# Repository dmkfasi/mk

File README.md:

# mk
# Redraw of arcade Mortal Kombat schematics

I actually messed up this a little bit.
The initial idea was to re-create original schematics from official arcade game manual. I started with freeware verions of
EAGLE, but then moved to KiCAD as an opensource alternative tool with no restrictions to the board size. I have completed
Sound Board only so far but never finished board layout due to high load of discrete components.

Other folders contains:
Arcade Cabinet - few FreeCAD drafts about the cabinet itself,
and
MultiKickHarness - a condenser board to hook up all the auxiliar Low Punch, Low Kick and Run buttons if you happen to have
multiple boards installed into a single cabinet.

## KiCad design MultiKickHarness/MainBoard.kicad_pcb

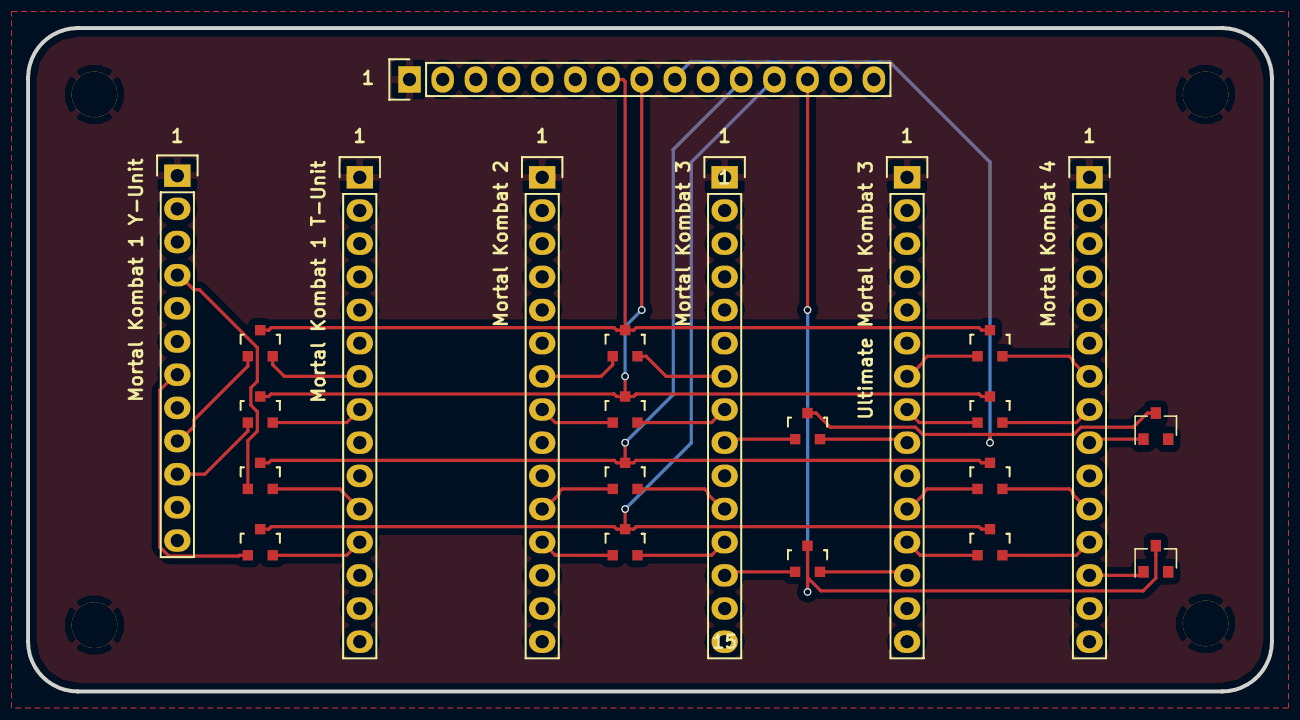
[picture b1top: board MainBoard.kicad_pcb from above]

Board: 2 copper layers, 95.3 x 50.8 mm, 27 parts (0 on the bottom side), 37 nets.

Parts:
D1, D2, D3: P2LP; SOT-23
D4, D5, D14: P2LK; SOT-23
D6, D11, D13: P1LK; SOT-23
D7, D8, D9: P1LP; SOT-23
D10, D15: P1RUN; SOT-23
D12, D16: P2RUN; SOT-23
J1: Mortal Kombat 1 Y-Unit; Pin_Header_Straight_1x12
J2: Mortal Kombat 1 T-Unit; Pin_Header_Straight_1x15
J3: Mortal Kombat 2; Pin_Header_Straight_1x15
J4: Mortal Kombat 3; Pin_Header_Straight_1x15
J5: Ultimate Mortal Kombat 3; Pin_Header_Straight_1x15
J6: Mortal Kombat 4; Pin_Header_Straight_1x15
P0, P0#2, P0#3, P0#4: MOUNTING HOLE; MountingHole_3-5mm
P1: TO CONTROL PANEL; Pin_Header_Straight_1x15

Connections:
/GND: J1.1, J2.1, J3.1, J4.1, J5.1, J6.1, P0.1, P0#2.1, P0#3.1, P0#4.1, P1.1
/P1-LK: D6.3, D11.3, D13.3, P1.8
/P1-LP: D7.3, D8.3, D9.3, P1.7
/P1-RUN: D10.3, D15.3, P1.9
/P2-LK: D4.3, D5.3, D14.3, P1.12
/P2-LP: D1.3, D2.3, D3.3, P1.11
/P2-RUN: D12.3, D16.3, P1.13
unnamed: D1.1, J1.4
unnamed: D1.2, J2.11
unnamed: D2.1, J3.11
unnamed: D2.2, J4.11
unnamed: D3.1, J5.11
unnamed: D3.2, J6.11
unnamed: D4.1, J1.7
unnamed: D4.2, J2.12
unnamed: D5.1, J3.12
unnamed: D5.2, J4.12
unnamed: D6.1, J1.10
unnamed: D6.2, J2.8
unnamed: D7.1, J1.9
unnamed: D7.2, J2.7
unnamed: D8.1, J3.7
unnamed: D8.2, J4.7
unnamed: D9.1, J5.7
unnamed: D9.2, J6.7
unnamed: D10.1, J4.9
unnamed: D10.2, J5.9
unnamed: D11.1, J3.8
unnamed: D11.2, J4.8
unnamed: D12.1, J4.13
unnamed: D12.2, J5.13
unnamed: D13.1, J5.8
unnamed: D13.2, J6.8
unnamed: D14.1, J5.12
unnamed: D14.2, J6.12
unnamed: D15.1, J6.9
unnamed: D16.1, J6.13

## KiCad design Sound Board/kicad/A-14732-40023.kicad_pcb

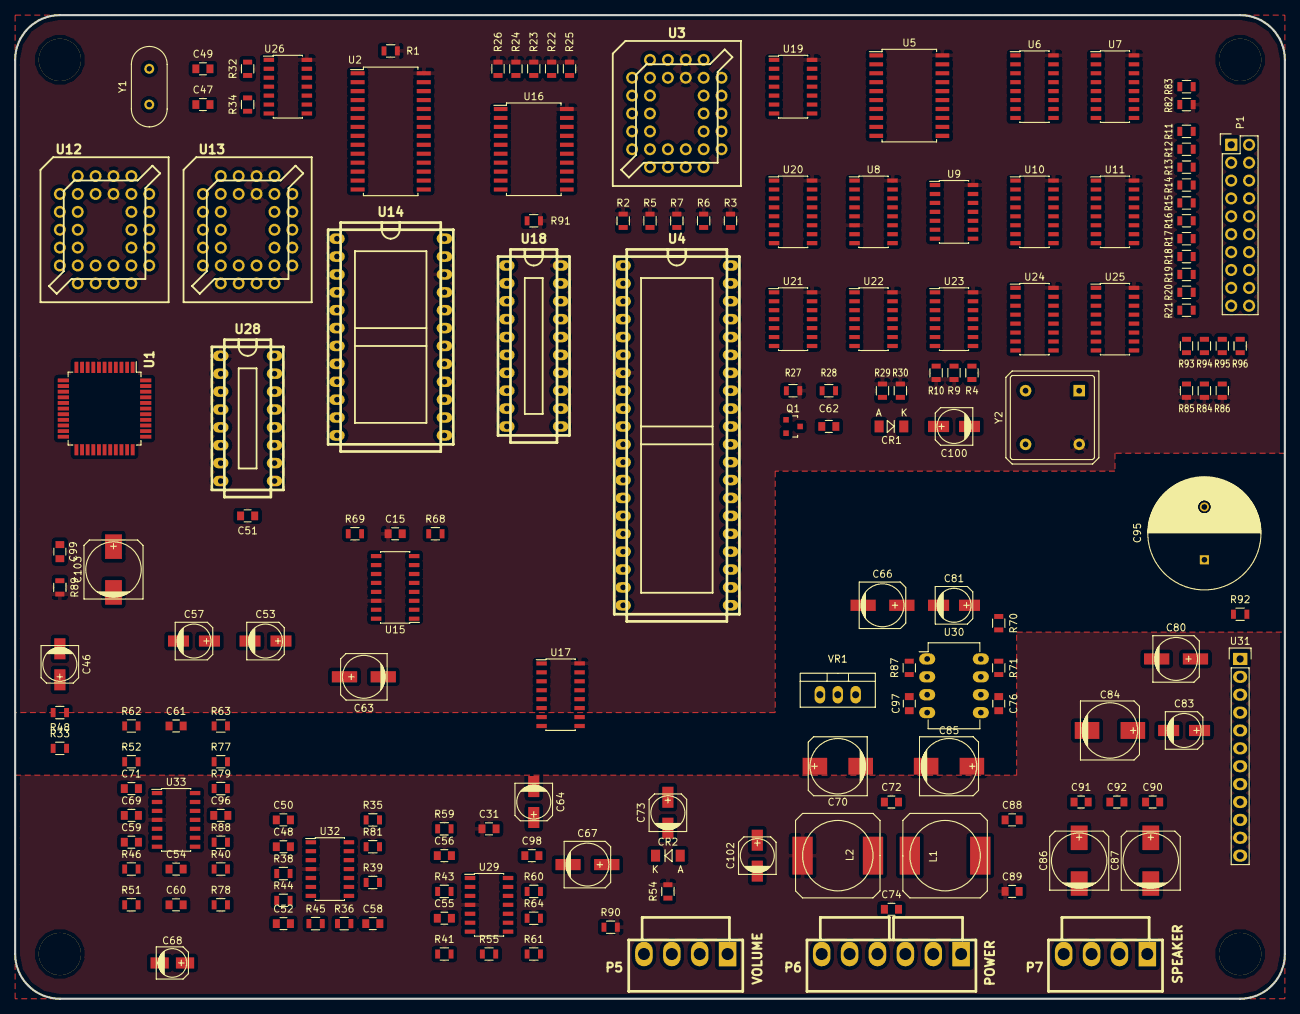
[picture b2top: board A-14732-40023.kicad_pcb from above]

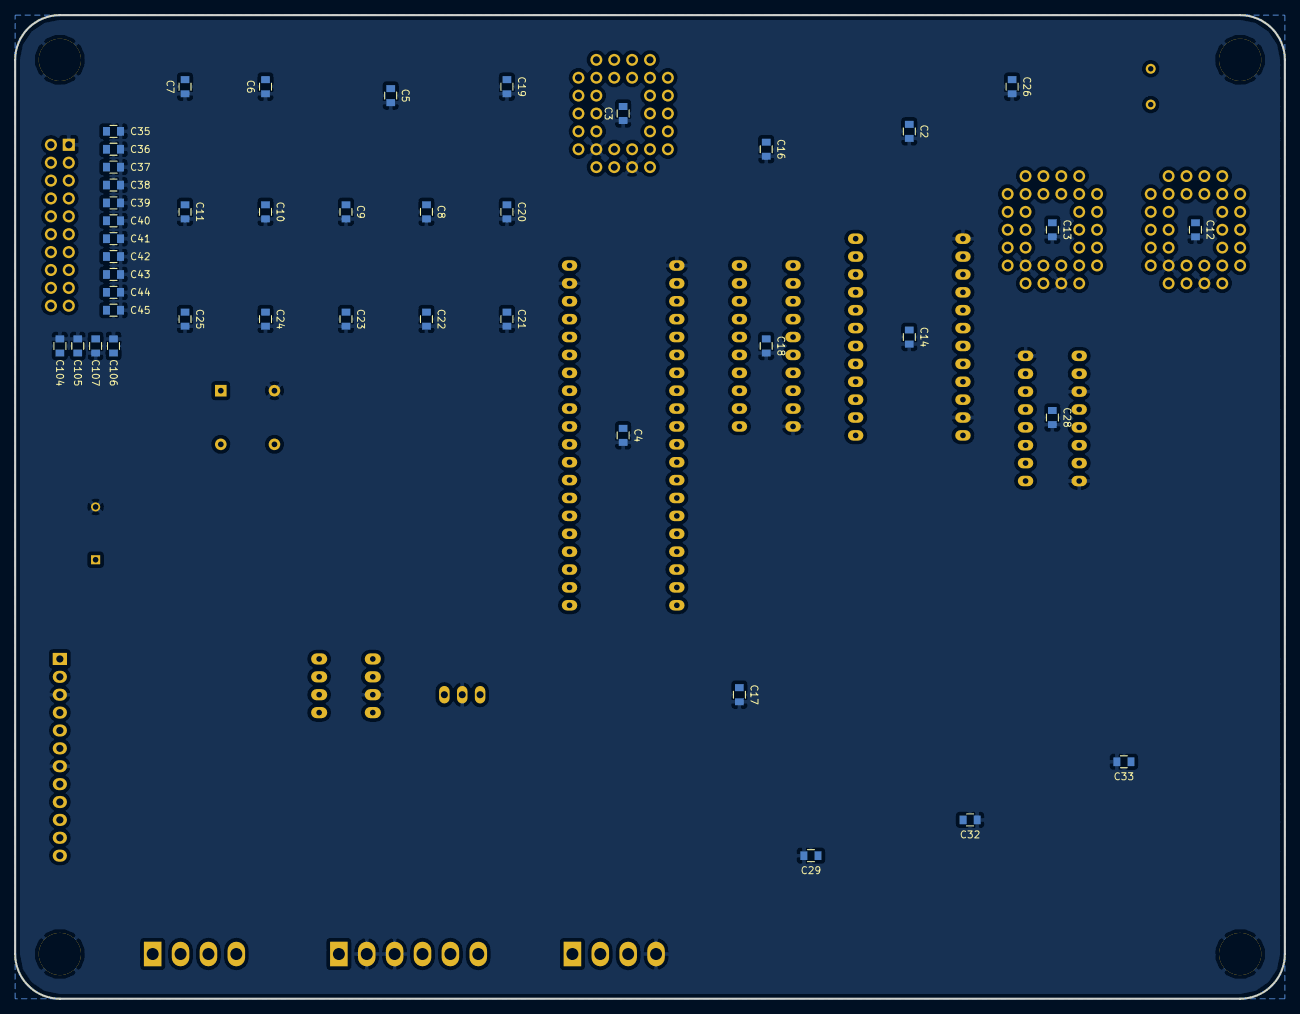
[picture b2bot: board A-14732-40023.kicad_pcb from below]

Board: 2 copper layers, 180.3 x 139.7 mm, 218 parts (43 on the bottom side), 235 nets, no tracks yet.

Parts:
C2, C4, C5, C8, C9, C10, C11, C12, C13, C14, C15, C16, C17, C18, C19, C20, C21, C22, C23, C24, C25, C26, C28, C29, C31, C33, C99: .01uF; C_0805
C3, C6, C7, C32, C97: 0.01uF; C_0805
C35, C36, C37, C38, C39, C40, C41, C42, C43, C44, C45, C47, C49, C98, C104, C105, C106, C107: 100pF; C_0805
C46, C53, C57, C64, C73, C81, C83, C100, C102: 10uF; c_elec_5x5.3
C48, C50, C51, C56: 3.3nF; C_0805
C52, C58: 6.8nF; C_0805
C54, C61, C96: 220pF; C_0805
C55: .001uF; C_0805
C59, C60: 33pF; C_0805
C62: 68pF; C_0805
C63, C66, C67, C80: 47uF; c_elec_6.3x5.3
C68: 1uF; c_elec_4x5.3
C69: 2.2nF; C_0805
C70, C85, C86, C87, C103: 100uF; c_elec_8x10
C71: 470pF; C_0805
C72, C74, C88, C89, C90, C91, C92: 0.1uF; C_0805
C76: 0.001uF; C_0805
C84: 220uF; c_elec_8x10
C95: 2200uF; C_Radial_D16_L25_P7.5
CR1: 1N4148; MiniMELF_Standard
CR2: 1N5232A; MiniMELF_Standard
L1, L2: 4.7uH; SELF-WE-PD-XXL
MTG1, MTG2, MTG3, MTG4: MTGHOLE; MountingHole_6mm
P1: CONN_02X10; Pin_Header_Straight_2x10
P5: VOLUME; kk156_26-60-4040
P6: POWER; kk156_26-60-4060
P7: SPEAKER; kk156_26-60-4040
Q1: MPS3646; SOT-23
R1, R2, R3, R5, R6, R7, R9, R10, R25, R84, R85, R86, R91: 4.7K; R_0805
R4, R30, R90: 100; R_0805
R11, R12, R13, R14, R15, R16, R17, R18, R19, R20, R21, R70, R93, R94, R95, R96: 47; R_0805
R22, R23, R24, R26, R59, R61: 2.2K; R_0805
R27: 150; R_0805
R28: 3.3K; R_0805
R29, R81: 47K; R_0805
R32, R34, R41, R83: 470; R_0805
R33, R38, R39, R48, R55, R60, R92: 100K; R_0805
R35, R36, R62, R63, R71: 10K; R_0805
R40, R44, R46, R52: 150K; R_0805
R43, R68: 1K; R_0805
R45, R51: 62K; R_0805
R54: 200; R_0805
R64: 12K; R_0805
R69: 8.2K; R_0805
R77, R78: 56K; R_0805
R79: 82K; R_0805
R82: 220; R_0805
R87: 3.9K; R_0805
R88: 27K; R_0805
R89: 10; R_0805
U1: OKI6295; LQFP-44_10x10mm_Pitch0.8mm
U2: 2064; SOIC-28_7.5x17.9mm_Pitch1.27mm
U3, U12, U13: 27C040-100; plcc32_pth-skt
U4: 6809E; dil_40-600_socket
U5, U16: 74ALS374; SOIC-20_7.5x12.8mm_Pitch1.27mm
U6, U10, U25: 26LS32A; SOIC-16_3.9x9.9mm_Pitch1.27mm
U7, U11, U24: 26LS31; SOIC-16_3.9x9.9mm_Pitch1.27mm
U8: 74ALS138; SOIC-16_3.9x9.9mm_Pitch1.27mm
U9, U22, U23: 74LS74; SOIC-14_3.9x8.7mm_Pitch1.27mm
U14: YM2151; dil_24-600_socket
U15: TIL7524; SOIC-16_3.9x9.9mm_Pitch1.27mm
U17: 74ALS174; SOIC-16_3.9x9.9mm_Pitch1.27mm
U18: 16L8-25; dil_20-300_socket
U19: 74LS11; SOIC-14_3.9x8.7mm_Pitch1.27mm
U20: 74ALS139; SOIC-16_3.9x9.9mm_Pitch1.27mm
U21: 74LS14; SOIC-14_3.9x8.7mm_Pitch1.27mm
U26: 74LS04; SOIC-14_3.9x8.7mm_Pitch1.27mm
U28: YM3012; dil_16-300_socket
U29: LM324D; SOIC-14_3.9x8.7mm_Pitch1.27mm
U30: MC3340; DIP-8_W7.62mm_LongPads
U31: MB3731; Pin_Header_Straight_1x12
U32, U33: TL084D; SOIC-14_3.9x8.7mm_Pitch1.27mm
VR1: 7809; TO-220_Neutral123_Vertical
Y1: 3.5749MHz; HC-49V
Y2: 8.0MHz; OSC_DIP8

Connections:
+5V: C2.1, C3.2, C4.1, C5.1, C6.2, C7.2, C8.1, C9.1, C10.1, C11.1, C12.1, C13.1, C14.1, C15.1, C16.1, C17.1, C18.1, C19.1, C20.1, C21.1, C22.1, C23.1, C24.1, C25.1, C26.1, C28.1, C70.1, C72.1, L1.1, R1.1, R2.1, R3.1, R5.1, R6.1, R7.1, R9.1, R10.1, R22.1, R23.1, R24.1, R25.1, R26.1, R27.1, R29.1, R30.1, R82.1, R84.2, R85.2, R86.2, R89.2, R91.1, U1.7, U2.28, U3.1, U3.32, U4.7, U5.20, U6.16, U7.16, U8.6, U8.16, U9.14, U10.16, U11.16, U12.1, U12.32, U13.1, U13.32, U14.22, U15.14, U16.20, U17.16, U18.20, U19.14, U20.16, U21.14, U22.14, U23.14, U24.16, U25.16, U26.14, U28.1, Y2.8
+9V: R69.2, U30.8, VR1.3
+12V: C29.1, C31.1, C32.2, C33.1, C85.1, C89.1, C95.1, L2.2, R54.2, R90.2, U29.4, U31.11, U32.4, U33.4, VR1.1
+12VDEC: C102.1, R48.1, R55.2, R90.1
/E: C62.1, R28.2, U18.5, U22.6, U23.2
/EORQ: U18.15, U20.1
/Q: U18.6, U23.6
/RD: U1.2, U2.22, U14.6, U18.18
/Video Sound Generator Interface/B_VIDDAV: C104.2, R96.1, U25.14
/Video Sound Generator Interface/B_VIDRES: C106.2, R85.1, R93.1, U25.6
/Video Sound Generator Interface/D0: U5.3, U6.3
/Video Sound Generator Interface/D1: U5.4, U6.5
/Video Sound Generator Interface/D2: U5.7, U6.11
/Video Sound Generator Interface/D3: U5.8, U6.13
/Video Sound Generator Interface/D4: U5.13, U10.3
/Video Sound Generator Interface/D5: U5.14, U10.5
/Video Sound Generator Interface/D6: U5.17, U10.11
/Video Sound Generator Interface/D7: U5.18, U10.13
/Video Sound Generator Interface/FFO: U9.9, U24.1
/Video Sound Generator Interface/SNDVIDRD: C105.2, R86.1, R95.1, U25.10
/Video Sound Generator Interface/SND_DAT0: C35.1, P1.3, R11.1
/Video Sound Generator Interface/SND_DAT1: C37.1, P1.4, R13.1
/Video Sound Generator Interface/SND_DAT2: C38.1, P1.5, R14.1
/Video Sound Generator Interface/SND_DAT3: C36.1, P1.6, R12.1
/Video Sound Generator Interface/SND_DAT4: C39.1, P1.7, R15.1
/Video Sound Generator Interface/SND_DAT5: C40.1, P1.8, R16.1
/Video Sound Generator Interface/SND_DAT6: C41.1, P1.9, R17.1
/Video Sound Generator Interface/SND_DAT7: C42.1, P1.10, R18.1
/Video Sound Generator Interface/SND_DAT8: C107.2, R84.1, R94.1, U25.2
/Video Sound Generator Interface/VIDSNDRD: U7.12, U9.13, U11.12, U25.11
/Video Sound Generator Music Synthesis/D0: U1.37, U14.10, U15.11, U17.4
/Video Sound Generator Music Synthesis/D1: U1.38, U14.12, U15.10, U17.14
/Video Sound Generator Music Synthesis/D2: U1.39, U14.13, U15.9, U17.6
/Video Sound Generator Music Synthesis/D3: U1.40, U14.14, U15.8
/Video Sound Generator Music Synthesis/D4: U1.41, U14.15, U15.7
/Video Sound Generator Music Synthesis/D5: U1.42, U14.16, U15.6
/Video Sound Generator Music Synthesis/D6: U1.43, U14.17, U15.5
/Video Sound Generator Music Synthesis/D7: U1.44, U14.18, U15.4
/Video Sound Generator Music Synthesis/PCM-A0: U1.18, U12.12, U13.12
/Video Sound Generator Music Synthesis/PCM-A1: U1.19, U12.11, U13.11
/Video Sound Generator Music Synthesis/PCM-A2: U1.20, U12.10, U13.10
/Video Sound Generator Music Synthesis/PCM-A3: U1.21, U12.9, U13.9
/Video Sound Generator Music Synthesis/PCM-A4: U1.22, U12.8, U13.8
/Video Sound Generator Music Synthesis/PCM-A5: U1.23, U12.7, U13.7
/Video Sound Generator Music Synthesis/PCM-A6: U1.24, U12.6, U13.6
/Video Sound Generator Music Synthesis/PCM-A7: U1.25, U12.5, U13.5
/Video Sound Generator Music Synthesis/PCM-A8: U1.26, U12.27, U13.27
/Video Sound Generator Music Synthesis/PCM-A9: U1.27, U12.26, U13.26
/Video Sound Generator Music Synthesis/PCM-A10: U1.28, U12.23, U13.23
/Video Sound Generator Music Synthesis/PCM-A11: U1.29, U12.25, U13.25
/Video Sound Generator Music Synthesis/PCM-A12: U1.30, U12.4, U13.4
/Video Sound Generator Music Synthesis/PCM-A13: U1.31, U12.28, U13.28
/Video Sound Generator Music Synthesis/PCM-A14: U1.32, U12.29, U13.29
/Video Sound Generator Music Synthesis/PCM-A15: U1.33, U12.3, U13.3
/Video Sound Generator Music Synthesis/PCM-A16: U1.34, U12.2, U13.2
/Video Sound Generator Music Synthesis/PCM-D0: U1.9, U12.13, U13.13
/Video Sound Generator Music Synthesis/PCM-D1: U1.10, U12.14, U13.14
/Video Sound Generator Music Synthesis/PCM-D2: U1.11, U12.15, U13.15
/Video Sound Generator Music Synthesis/PCM-D3: U1.12, U12.17, U13.17
/Video Sound Generator Music Synthesis/PCM-D4: U1.13, U12.18, U13.18
/Video Sound Generator Music Synthesis/PCM-D5: U1.14, U12.19, U13.19
/Video Sound Generator Music Synthesis/PCM-D6: U1.15, U12.20, U13.20
/Video Sound Generator Music Synthesis/PCM-D7: U1.16, U12.21, U13.21
/Video Sound Generator Speech Synthesis/A1: U2.9, U3.11, U4.9
/Video Sound Generator Speech Synthesis/A2: U2.8, U3.10, U4.10
/Video Sound Generator Speech Synthesis/A3: U2.7, U3.9, U4.11
/Video Sound Generator Speech Synthesis/A4: U2.6, U3.8, U4.12
/Video Sound Generator Speech Synthesis/A5: U2.5, U3.7, U4.13
/Video Sound Generator Speech Synthesis/A6: U2.4, U3.6, U4.14
/Video Sound Generator Speech Synthesis/A7: U2.3, U3.5, U4.15
/Video Sound Generator Speech Synthesis/A8: U2.25, U3.27, U4.16
/Video Sound Generator Speech Synthesis/A9: U2.24, U3.26, U4.17
/Video Sound Generator Speech Synthesis/A10: U2.21, U3.23, U4.18, U8.1
/Video Sound Generator Speech Synthesis/A11: U2.23, U3.25, U4.19, U8.2
/Video Sound Generator Speech Synthesis/A12: U2.2, U3.4, U4.20, U8.3
/Video Sound Generator Speech Synthesis/A13: U3.28, U4.21, U20.13
/Video Sound Generator Speech Synthesis/A14: U4.22, U20.3
/Video Sound Generator Speech Synthesis/A15: U3.29, U4.23, U20.2
/Video Sound Generator Speech Synthesis/D0: U2.11, U3.13, U4.31, U16.3
/Video Sound Generator Speech Synthesis/D1: U2.12, U3.14, U4.30, U16.4
/Video Sound Generator Speech Synthesis/D2: U2.13, U3.15, U4.29, U16.7
/Video Sound Generator Speech Synthesis/D3: U2.15, U3.17, U4.28, U16.8
/Video Sound Generator Speech Synthesis/D4: U2.16, U3.18, U4.27
/Video Sound Generator Speech Synthesis/D5: U2.17, U3.19, U4.26
/Video Sound Generator Speech Synthesis/D6: U2.18, U3.20, U4.25
/Video Sound Generator Speech Synthesis/D7: U2.19, U3.21, U4.24
/Video Sound Generator Speech Synthesis/RAM/CS: U2.20, U20.12
/WR: U1.3, U2.27, U14.5, U15.13, U18.19
A0: U2.10, U3.12, U4.8, U14.4
ADPCM: U1.4, U8.12
ADPCMCLK: U1.5, U9.5
ATE1: R25.2, U9.10, U9.12, U16.13, U16.14, U16.17, U16.18, U18.8, U19.9, U23.13, U24.4, U24.9, U25.4
ATE_CLR: R9.2, U9.1, U17.1, U22.1, U22.13, U23.1
BS0: U17.5, U18.1
BS1: U17.15, U18.2
BS2: U17.7, U18.3, U19.10
DAC: U8.13, U15.12
DAC-OUT: R61.2, R62.1, U29.8, U29.9
FIRQ: R7.2, U4.4, U14.2
GND: C2.2, C3.1, C4.2, C5.2, C6.1, C7.1, C8.2, C9.2, C10.2, C11.2, C12.2, C13.2, C14.2, C15.2, C16.2, C17.2, C18.2, C19.2, C20.2, C21.2, C22.2, C23.2, C24.2, C25.2, C26.2, C28.2, C29.2, C31.2, C32.1, C33.2, C35.2, C36.2, C37.2, C38.2, C39.2, C40.2, C41.2, C42.2, C43.1, C44.1, C45.1, C48.2, C49.2, C50.2, C51.2, C54.1, C56.2, C61.1, C63.2, C64.2, C66.2, C69.1, C70.2, C72.2, C73.2, C74.2, C76.1, C80.2, C83.2, C84.2, C85.2, C88.2, C89.2, C90.1, C91.1, C95.2, C97.1, C98.2, C99.2, C100.2, C102.2, C103.2, C104.1, C105.1, C106.1, C107.1, CR2.2, MTG1.1, MTG2.1, MTG3.1, MTG4.1, P1.1, P5.4, P6.2, P6.3, Q1.1, R4.2, R33.2, R41.1, R59.1, R60.1, R61.1, R68.1, R70.2, R83.2, U1.1, U2.14, U3.16, U3.22, U4.1, U4.39, U5.10, U6.4, U6.8, U7.4, U7.8, U8.8, U9.7, U10.4, U10.8, U11.4, U11.8, U12.16, U12.22, U13.16, U13.22, U14.1, U14.11, U15.2, U15.3, U16.10, U17.8, U18.10, U19.7, U20.8, U20.14, U21.7, U22.7, U23.7, U24.8, U25.8, U26.7, U28.3, U28.8, U28.16, U29.11, U30.3, U31.3, U31.7, U32.11, U33.11, VR1.2, Y2.4
IRQ: R5.2, U4.3, U23.9, U24.15
MIX-OUT: C68.2, U30.1
unnamed: C43.2, P1.11, R19.1
unnamed: C44.2, P1.15, R20.1
unnamed: C45.2, P1.19, R21.1
unnamed: C46.1, R33.1, R48.2, U32.3
unnamed: C46.2, U1.36
unnamed: C47.1, Y1.2
unnamed: C47.2, R34.1, U26.4, U26.5
unnamed: C48.1, R36.1, U32.5
unnamed: C49.1, R32.2, U26.1, Y1.1
unnamed: C50.1, R38.2, U32.12
unnamed: C51.1, C53.2, U28.9
unnamed: C52.1, R35.2, U32.13, U32.14
unnamed: C52.2, R38.1, R39.1
unnamed: C54.2, R44.2, R45.2, R46.1
unnamed: C55.1, U28.14, U29.6
unnamed: C55.2, R41.2, U28.13, U29.7
unnamed: C56.1, C57.2, U28.10
unnamed: C58.2, R35.1, R36.2
unnamed: C59.1, R46.2, U32.9
unnamed: C59.2, R45.1, R78.2, U32.8
unnamed: C60.1, R52.2, U33.6
unnamed: C60.2, R51.1, R77.2, U33.7
unnamed: C61.2, R40.2, R51.2, R52.1
unnamed: C62.2, Q1.2, R28.1
unnamed: C63.1, R68.2, R69.1, U15.1
unnamed: C64.1, U28.15, U29.5
unnamed: C66.1, C97.2, R87.1, U30.2
unnamed: C67.1, R55.1, R60.2, U29.10
unnamed: C67.2, R59.2, U29.13, U29.14
unnamed: C68.1, C96.1, R88.1, U33.14
unnamed: C69.2, R62.2, R63.2, R64.1
unnamed: C71.1, R64.2, U33.2
unnamed: C71.2, R63.1, R79.2, U33.1
unnamed: C73.1, CR2.1, R54.1, U32.10, U33.3, U33.5, U33.12
unnamed: C74.1, L1.2, P6.1
unnamed: C76.2, U30.5
unnamed: C80.1, U31.6
unnamed: C81.1, R70.1, R71.2
unnamed: C81.2, R92.2, U31.1
unnamed: C83.1, U31.4
unnamed: C84.1, R92.1, U31.5
unnamed: C86.1, U31.9
unnamed: C86.2, C90.2, C91.2, C92.1, P7.3, P7.4, U31.8
unnamed: C87.1, U31.12
unnamed: C87.2, C92.2, P7.1, P7.2, U31.10
unnamed: C88.1, L2.1, P6.5, P6.6
unnamed: C96.2, R77.1, R78.1, R79.1, R81.1, R88.2, U33.13
unnamed: C98.1, U15.15, U29.12
unnamed: C100.1, CR1.2, R29.2, U21.9
unnamed: C99.1, C103.1, R89.1, U1.17
unnamed: CR1.1, R30.2
unnamed: P1.13, R96.2
unnamed: P1.16, R95.2
unnamed: P1.17, R93.2
unnamed: P1.18, R94.2
unnamed: P5.2, R87.2
unnamed: Q1.3, R27.2, U4.34
unnamed: R1.2, U2.26
unnamed: R2.2, U4.2
unnamed: R3.2, U4.40
unnamed: R4.1, U5.1, U23.12, U24.12, U25.12
unnamed: R10.2, U9.4, U22.4, U22.10, U22.11, U22.12, U23.4
unnamed: R11.2, U6.2, U7.2
unnamed: R12.2, U6.14, U7.14
unnamed: R13.2, U6.6, U7.6
unnamed: R14.2, U6.10, U7.10
unnamed: R15.2, U10.2, U11.2
unnamed: R16.2, U10.6, U11.6
unnamed: R17.2, U10.10, U11.10
unnamed: R18.2, U10.14, U11.14
unnamed: R19.2, U24.14
unnamed: R20.2, U24.6
unnamed: R21.2, U24.2
unnamed: R22.2, U3.30, U16.6
unnamed: R23.2, U3.2, U16.5
unnamed: R24.2, U3.3, U16.2
unnamed: R26.2, U3.31, U16.9
unnamed: R32.1, R34.2, U26.2, U26.3
unnamed: R39.2, U32.1, U32.2
unnamed: R43.1, U29.1, U29.2
unnamed: R43.2, U28.11
unnamed: R71.1, U30.7
unnamed: R82.2, R83.1, U6.1, U6.7, U6.9, U6.15, U10.1, U10.7, U10.9, U10.15, U25.1, U25.7, U25.9, U25.15
unnamed: R91.2, U18.7
unnamed: U5.2, U7.1
unnamed: U5.5, U7.7
unnamed: U5.6, U7.9
unnamed: U5.9, U7.15
unnamed: U9.2, U9.6
unnamed: U5.12, U11.1
unnamed: U5.15, U11.7
unnamed: U5.16, U11.9
unnamed: U5.19, U11.15
unnamed: U12.24, U19.8, U26.11
unnamed: U13.24, U26.10
unnamed: U14.19, U28.5
unnamed: U14.20, U28.6
unnamed: U14.21, U28.4
unnamed: U14.23, U28.2
unnamed: U14.24, U26.6
unnamed: U16.1, U26.8
unnamed: U8.15, U16.11
unnamed: U3.24, U18.11, U19.6
unnamed: U19.1, U21.2
unnamed: U19.3, U20.5
unnamed: U19.4, U20.6
unnamed: U19.5, U20.7, U26.9
unnamed: U19.11, U26.12
unnamed: U8.4, U8.5, U20.11
unnamed: U20.4, U20.15
unnamed: U21.1, U21.8
unnamed: U21.5, Y2.5
unnamed: U21.6, U22.3, U23.3
unnamed: U4.35, U22.2, U23.5
unnamed: U9.3, U22.5
unnamed: U23.11, U25.13
unnamed: U28.12, U29.3
PCM-A17: U1.35, U18.4, U26.13
PCM-BS: U8.10, U17.9
PCM-OUT: C58.1, R81.2, U32.6, U32.7
R/W: U4.32, U18.9
RA17-0: U12.30, U18.17
RA17-1: U13.30, U18.14
RA18-0: U12.31, U18.12
RA18-1: U13.31, U18.13
RD-LATCH: U6.12, U8.11, U10.12, U23.10, U24.7
RESET: R6.2, U1.8, U4.37, U14.3, U19.12, U28.7
SOFT_RES: U19.13, U25.3
VIDPWRON: U19.2, U25.5
WR-LATCH: U5.11, U8.7, U9.11
YAM: U8.14, U14.7
YAM1-OUT: C53.1, R40.1
YAM2-OUT: C57.1, R44.1

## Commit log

2015-09-28 4th sheet added
2015-09-28 Removed undo files
2015-09-28 new components added
2015-09-28 fixed packages
2015-10-03 auto regenerated, nothing useful yet
2015-10-05 almost complete 4th sheet
2015-10-05 shortened 26ls31, 26ls32 to fit vertical space
2015-10-06 autogen updated
2015-10-06 P1 connected mostly wired up
2015-10-06 overwritten with new software version
2015-10-09 nothing really new
2015-10-09 completed 4th sheet, some parts name corrected
2015-10-10 regenerated
2015-10-10 26ls32 outputs dir corrected
2015-10-10 fixed YAM-OUT2 net connection, fixed mixed up GND<->AGND, fixed missed power supply pins for U5
2015-10-10 approved non-critical warnings for power supply pins
2015-10-10 approved non-critical power pins warnings
2015-10-10 first revision for 40023 assembly and T-Unit CPU board
2015-10-10 1N5232 SOT-23 package added
2015-10-10 R65 replaced with CR2 according to the official schematics
2015-10-10 1N5232 MiniMELF package added
2015-10-10 updated values, names, fixed some parts, added C104-C107 and R94-R96
2015-10-10 current version
2015-10-11 small fixes, WIP
2015-10-11 added polarized capacitors for PANASONIC_C package
2015-10-11 replaced all non-power rail resistors to 0805 size 1/8W
2015-10-11 replaced filter capacitors to 0805 size
2015-10-11 current project
2015-10-11 replaced all the polarized capacitors with PANASONIC_? package, fixed bugs, replaced C95 with a hole-through
2015-10-11 Rework of the original board with more or less modern component base
2015-10-11 fixes
2015-10-11 initial layout after autogeneration
2015-10-11 SOP28 package added for 6264 SRAM chip
2015-10-11 added PLCC32 package and socket for ROM chips
2015-10-11 corrected library for SRAM and ROM chips
2015-10-11 updated other ICs with current library in use
2015-10-11 C79 corrected to C84
2015-10-11 layout WIP
2015-10-12 corrected C30 to C59
2015-10-12 Trying to lay around, resulting in fixing misplaced components and other fixes
2015-10-18 board layout wip
2015-10-26 no need for these
2015-11-01 Moving from EAGLE to KiCad, sorting out files
2015-11-01 moving eagle files
2015-11-01 Initial KiCad project files
2015-11-01 updated components description
2015-11-01 current files
2015-11-01 moved to hierarchy sheets, added sheet #2
2015-11-03 hierarchically sheets added
2015-11-03 another attempt, still hopeless
2015-11-03 some fixes
2015-11-04 74LS174 added, other components fixes
2015-11-04 current settings
2015-11-04 fixes to MTGHOLE added size
2015-11-04 work in progress, U1, U12, U13 added
2015-11-08 OpAmp added, TIL7524 added
2015-11-08 finished
2015-11-08 re-annoted components due to moving the sheet
2015-11-08 re-annoted components due to errors
2015-11-08 some DRC errors fixed
2015-11-08 power pins corrected, bi-dir pins corrected
2015-11-08 critical DRC errors fixes
2015-11-08 sheet 3 added, power rails added to fix current ERC errors
2015-11-08 sheet 4 yet is blank
2015-11-08 added 0.156" header, midified power supply pins
2015-11-08 sheet 3 and sheet 4 added
2015-11-08 power related ERC error fixes
2015-11-11 4-6 pin connector added
2015-11-11 minor fixes
2015-11-11 work in progress, started mc3340 wiring
2015-11-15 minor fixes for labels alignment
2015-11-15 work in progress around U30/U31
2015-11-15 global labels added as initial work in progress
2015-11-21 i/o buffers size compacted to fit paper frame
2015-11-21 work in progress due to changes in library
2015-11-21 work in progress on i/o buffers connections and placement
2015-11-22 Initial drawning for control panel based on dimensions references by Twistedsymphony and Jakobud.com
2015-11-23 updated with support, top glass cover and rounded side panels
2015-11-25 reference photographs
2015-11-25 completed back side support and fixed width for metric system
2015-11-30 74LS74A added to fit sheet4
2015-11-30 work in progress, wiring i/o buffers, trying to fit everything in place
2015-12-04 Work in progress
2015-12-04 Test assembly
2015-12-04 MK2 and later version
2015-12-04 Body side panels
2015-12-04 cleaned up a little
2015-12-20 more work in progress, P1 parallel interface added, SND_DAT signals connected
2015-12-26 revert sizes back for 26LS31 and 26LS32 due to paper size of Sheet4
2015-12-26 changed properies for sheet4 title
2015-12-26 updated with last date
2015-12-26 corrected c104-c107, connected U10 INs
2015-12-26 finished with OpAMP U31
2015-12-26 finished, revised
2015-12-26 fiddle some stuff around for the best fit
2015-12-26 corrected P7 speaker out
2015-12-26 cleaned up
2015-12-26 A0 global label for Yamaha CPU added
2015-12-26 A0 global label connected to CPU address bus
2015-12-26 OpAMP positive feedback input pulled up 12V with Zener diode
2016-01-12 updated footprints, work in progress
2016-01-15 oscillator rework for DIL8 package
2016-01-15 current library
2016-01-15 updating footprints
2016-01-24 Open Hardware License
2016-01-24 Revision 2 schematic
2016-01-24 Revision 1 board layout
2016-01-24 Current netlist
2016-01-24 Revision 2
2016-01-24 Revision 2 cleaned up
2016-01-24 Fabrication files
2016-02-06 Updated footprints
2016-02-06 New euroboard layout 160x100mm with rounded corners and mounting holes
2016-02-12 New layout for larger board of 180x120mm
2016-02-12 now using pin header as package for U31 to display more or less properly in a 3D view
2016-02-12 current layout for 180x120mm size
2016-02-12 changed package for U31 to pin header for proper display in 3D PCB view
2016-02-14 All components placed, time to play around
2016-02-14 fiddling around
2016-02-18 playing-laying
2016-02-19 playing around
2016-03-08 Upgraded to FreeCAD 0.16, mounting axis A4 template created for actual application
2016-03-08 Printable template for drilling button holes
2016-03-27 Moved ruler to User.drwg, slightly narrowed board for better sit of P1 control panel connector and moved its name to a place where it is going to be visible after soldering angled pin header
2016-03-27 new production files for fixed PCB
2017-01-17 Update README.md
    typos
2017-01-23 New layout
2017-01-23 New netlist
2017-01-23 Redraw with SOT-23 diodes for MK4 RUN buttons
2017-01-23 Complete Rev.2.1
2017-01-23 Revision 2.1 gerber file
2017-01-23 PCB render image
2017-01-24 New mount drill positions
2017-01-24 New mount hole positions
2017-01-24 Updated look, red coating
